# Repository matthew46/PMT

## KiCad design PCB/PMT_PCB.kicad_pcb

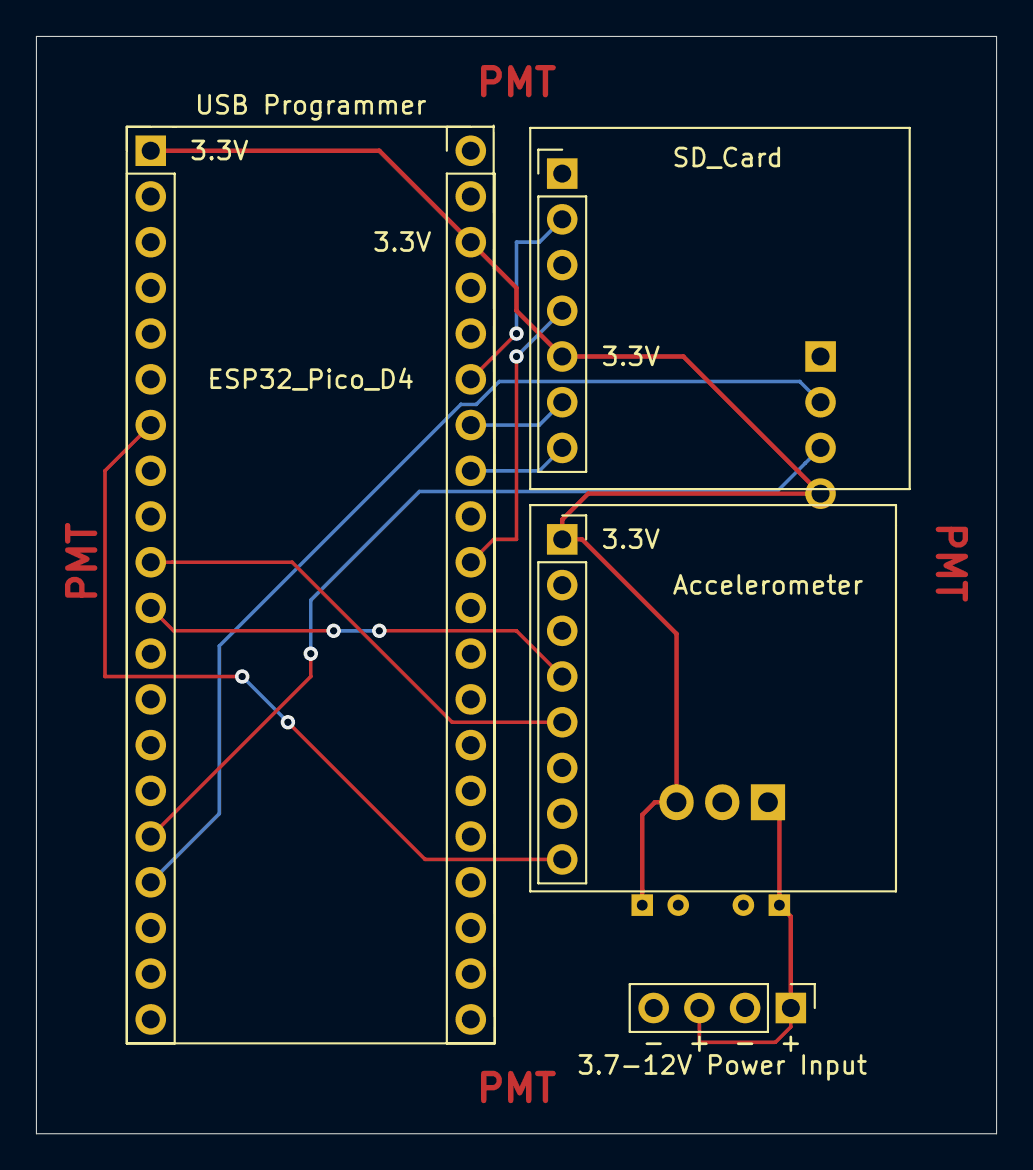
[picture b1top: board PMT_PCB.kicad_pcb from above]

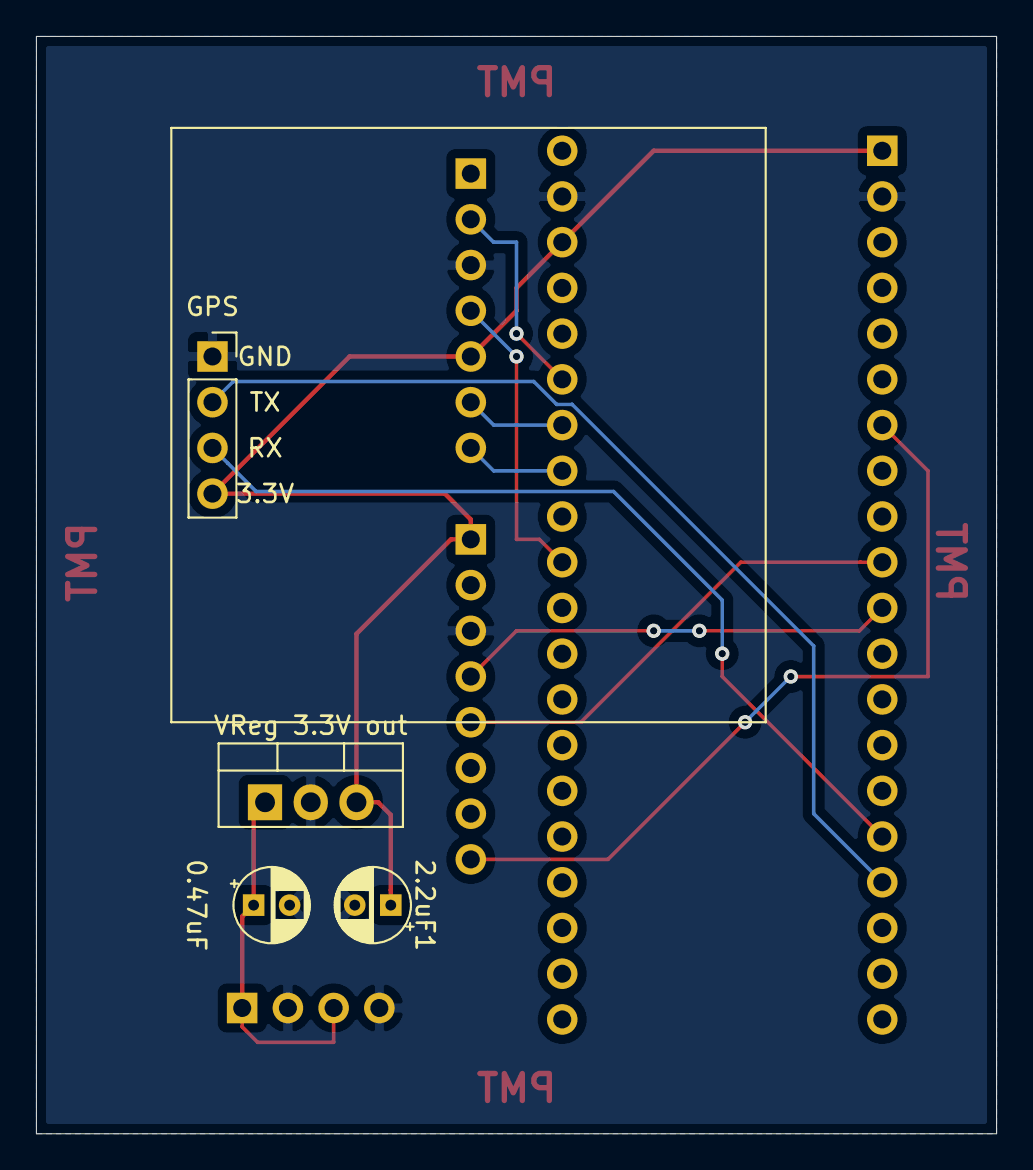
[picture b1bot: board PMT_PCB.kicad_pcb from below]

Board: 2 copper layers, 53.3 x 61.0 mm, 8 parts (4 on the bottom side), 12 nets.

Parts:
0.47uF, 2.2uF1: C; CP_Radial_D4.0mm_P2.00mm
3.7-12V Power Input: Conn_01x04; PinHeader_1x04_P2.54mm_Vertical
Accelerometer: Conn_01x08; Accelerometer_Breakout
ESP32_Pico_D4: ESP32_Pico_D4
GPS: .; GPS
SD_Card: Conn_01x07; SD_Card_Breakout
VReg 3.3V out: AZ2940; TO-220-3_Vertical

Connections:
3.3V: 2.2uF1.1, Accelerometer.1, ESP32_Pico_D4.1, ESP32_Pico_D4.38, GPS.4, SD_Card.5, VReg 3.3V out.3
3.7-12Vin: 0.47uF.1, 3.7-12V Power Input.1, 3.7-12V Power Input.3, VReg 3.3V out.1
ACCEL_INT1: Accelerometer.8, ESP32_Pico_D4.7
ACCEL_SCL: Accelerometer.4, ESP32_Pico_D4.11
ACCEL_SDA: Accelerometer.5, ESP32_Pico_D4.10
GND: 0.47uF.2, 2.2uF1.2, 3.7-12V Power Input.2, 3.7-12V Power Input.4, Accelerometer.3, ESP32_Pico_D4.2, ESP32_Pico_D4.39, GPS.1, SD_Card.3, VReg 3.3V out.2
GPS_RX: ESP32_Pico_D4.16, GPS.3
GPS_TX: ESP32_Pico_D4.17, GPS.2
SD_CS: ESP32_Pico_D4.33, SD_Card.7
SD_DI: ESP32_Pico_D4.34, SD_Card.6
SD_DO: ESP32_Pico_D4.35, SD_Card.2
SD_SCK: ESP32_Pico_D4.31, SD_Card.4

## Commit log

2020-01-01 Created tools folder
    Place old code that is still useful to you in development and should not be changed/altered/deleted by anyone
2020-01-01 Moved many things around
    Structured all module "main" files to be under a single main.
    PMT_main.c will act as our new main.c
    All module files should be created as supporting header files to be included and called from PMT_main.c
2020-01-01 not needed
    contents moved into GNSS.h
2020-01-13 SD Card Python
2020-02-29 Fixed Accelerometer Pinout
2020-03-03 Removed Accel Folder
2020-03-13 nothing
2020-03-20 PCB Version 1
2020-03-21 PCB Version 2
2020-03-21 PCB Revision #2
2020-03-21 Deleted PCB Folder
2020-03-21 PCB Revision #2 (Fixed Schematic)
